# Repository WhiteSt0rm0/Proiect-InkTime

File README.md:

# Proiect InkTime

An affordable, open-source smartwatch powered by the nRF52840 with an e-paper display, designed for low power consumption and BLE connectivity.

## Table of Contents

1. [Hardware Diagram](#hardware-diagram)
2. [Bill of Materials](#bill-of-materials-bom)
3. [Hardware Description](#hardware-description)
4. [Pin Assignment](#nrf52840-pin-assignment)
5. [PCB Design Details](#pcb-design-details)

---

## Hardware Diagram

The InkTime smartwatch is built around the Nordic nRF52840 microcontroller and features the following subsystems:

```
                                    ┌───────────────────┐
                                    │    USB-C (J4)     │
                                    └──┬─────────────┬──┘
                                 VBUS  │             │ D+, D-
                                       │      ┌──────▼────────┐
                          ┌────────────┤      │  USBLC6 (D3)  │
                          │            │      │ ESD Protection│
                          │            │      └──────┬────────┘
                          │            │             │ D+, D- (protected)
                   ┌──────▼────────┐   │      ┌──────▼─────────────────────────┐
                   │  BQ25180 (IC3)│   │      │                                │
                   │  LiPo Charger │   │      │        nRF52840 (NRF52840_QF)  │
                   │  (I2C config) │   │      │        ARM Cortex-M4F @ 64MHz  │
                   └──────┬────────┘   │      │        BLE 5.0                 │
                          │            │      │                                │
                    VBAT  │     VBUS   │      │  ┌─────────────────────────┐   │
          ┌───────────────┤◄───────────┘      │  │ Interfaces:             │   │
          │               │                   │  │  SPI  → E-Paper Display │   │
   ┌──────▼────────┐      │                   │  │  I2C  → BMA423, DRV2605 │   │
   │ LiPo Battery  │      │                   │  │         MAX17048,       │   │
   │ LP502030      │      │                   │  │         BQ25180, RT6160 │   │
   │ 3.7V / 250mAh │      │                   │  │  USB  → USB-C (J4)      │   │
   └──────┬────────┘      │                   │  │  GPIO → Buttons, EPD    │   │
          │ VBAT          │                   │  │         ctrl, Haptic EN │   │
   ┌──────▼────────┐      │                   │  │  SWD  → TC2030 (J1)     │   │
   │ MAX17048 (U1) │──────│── I2C ───────────►│  └─────────────────────────┘   │
   │ Fuel Gauge    │      │                   │                                │
   │ (ALERT → GPIO)│      │                   │◄──── 32MHz Crystal (X1)        │
   └───────────────┘      │                   │◄──── 32.768kHz Crystal (X2)    │
                          │                   │◄──── 2.4GHz Antenna (ANT1)     │
                   ┌──────▼────────┐          │      via matching network      │
                   │  RT6160 (IC1) │          │      (L1, C3, C4, C9)          │
                   │  DC/DC        │          │                                │
                   │  Buck-Boost   │ VREG/3V3 │                                │
                   │  (I2C config) ├─────────►│                                │
                   └───────────────┘          └──┬──────┬──────┬───────────┬───┘
                                                 │      │      │           │
                              SPI (MOSI,SCK,CS)  │      │      │           │ GPIO
                              + GPIO ctrl        │      │ I2C  │ I2C       │ (SW_UP P0.26)
                                                 │      │      │           │ (SW_DN P0.27)
                  ┌──────────────────────┐       │      │      │       ┌───▼──────────────────┐
                  │  1.54" E-Paper (J2)  │◄──────┘      │      │       │  3×        Buttons   │
                  │  200×200px SPI       │              │      │       │  EVP-AKE31A          │
                  │                      │              │      │       │  (SW_ENT P1.00)      │
                  │  EPD Boost Circuit:  │              │      │       └──────────────────────┘
                  │  Q1 (DMG2305UX)      │              │      │
                  │  Q3 (SI1308EDL)      │       ┌──────▼──┐   │
                  │  D2,D4,D5 (MBR0530)  │       │ BMA423  │   │
                  │  L5 (68µH)           │       │  (IC2)  │   │
                  │  → PREVGH, PREVGL    │       │  IMU    │   │
                  └──────────────────────┘       └─────────┘   │
                                                        ┌──────▼──────┐
                           ┌──────────────┐             │  DRV2605    │
                           │  TC2030 (J1) │             │   (IC4)     │
                           │  SWD Debug   │             │  Haptic     │
                           │  (SWDIO,     │             │  Driver     │
                           │   SWDCLK,    │             │  + Motor    │
                           │   SWO, RST)  │             │  (FIT0774)  │
                           └──────────────┘             └─────────────┘
```

---

## Bill of Materials (BOM)

| Component | Value / Part Number | Package | Qty | Description | Datasheet |
|-----------|---------------------|---------|-----|-------------|-----------|
| NRF52840_QF | nRF52840 | QFN-73 | 1 | MCU with BLE 5.0 | [Link](datasheet-link) |
| IC1 | RT6160 | AWSCWL-CSP-15 | 1 | DC/DC Buck-Boost Converter | [Link](datasheet-link) |
| IC2 | BMA423 | LGA-12 | 1 | Triaxial Accelerometer (IMU) | [Link](datasheet-link) |
| IC3 | BQ25180 | YBGRDS-BGA-8 | 1 | LiPo Charger | [Link](datasheet-link) |
| IC4 | DRV2605 | YZFR-WCSP-9 | 1 | Haptic Driver | [Link](datasheet-link) |
| U1 | MAX17048 | G+T10-TDFN-8 | 1 | Fuel Gauge | [Link](datasheet-link) |
| D3 | USBLC6-2SC6Y | SOT-23-6 | 1 | ESD Protection | [Link](datasheet-link) |
| ANT1 | 2450AT18B100E | SMD | 1 | 2.4GHz Chip Antenna | [Link](datasheet-link) |
| X1 | 32MHz Crystal | SMD 2016 | 1 | Main Clock | - |
| X2 | 32.768kHz Crystal | SMD 3215 | 1 | RTC Clock | - |
| J1 | TC2030-IDC | Tag-Connect | 1 | SWD Debug Header | [Link](datasheet-link) |
| J2 | 503480-2400 | FPC-24 | 1 | E-Paper FPC Connector | [Link](datasheet-link) |
| J4 | KH-TYPE-C-16P | SMD | 1 | USB-C Connector | - |
| Q1 | DMG2305UX-7 | SOT-23 | 1 | P-Ch MOSFET (EPD drive) | [Link](datasheet-link) |
| Q3 | SI1308EDL-T1-GE3 | SC-70 | 1 | N-Ch MOSFET (EPD drive) | [Link](datasheet-link) |
| D2, D4, D5 | MBR0530 | SOD-123 | 3 | Schottky Diode (EPD drive) | - |
| L1 | 3.9nH | SMD 2012 | 1 | RF Matching Network | - |
| L2 | 10µH | SMD 2012 | 1 | nRF Power Inductor | - |
| L3 | 15nH | SMD 2012 | 1 | RF Filter | - |
| L5 | 68µH | SMD 2012 | 1 | EPD Boost Inductor | - |
| L7 | FTC252012SR47M-BCA | SMD 2012 | 1 | DC/DC Power Inductor (0.47µH) | - |
| SW_UP, SW_DN, SW_ENT | EVP-AKE31A | SMD | 3 | Tactile Buttons | - |
| SJ1 | Solder Jumper | SMD | 1 | Configuration Jumper | - |
| R1, R2, R5 | 0Ω | 0201 | 3 | Zero-ohm Resistors | - |
| R3, R4 | 3.3kΩ | 0201 | 2 | I2C Pull-up Resistors | - |
| R6, R2_EP_DR, R_PWR_EPD | 10kΩ | 0201 | 3 | Pull-up/Pull-down | - |
| R7, R8, R9 | 10kΩ | 0201 | 3 | Button Pull-down Resistors | - |
| R1_USB, R2_USB | 5.1kΩ | 0201 | 2 | USB-C CC Pull-down | - |
| R_TYPE_SEL | 2.2Ω | 0201 | 1 | EPD Type Select | - |
| R1_EP_DR | 0.47Ω | 0201 | 1 | EPD Current Sense | - |
| C1, C2, C17, C18 | 12pF | 0201 | 4 | Crystal Load Capacitors | - |
| C3, C4 | 1pF | 0201 | 2 | RF Matching | - |
| C9 | 820pF | 0201 | 1 | RF Matching | - |
| C5, C7, C8, C12, C19 | 100nF | 0201 | 5 | Decoupling Capacitors | - |
| C11 | 100pF | 0201 | 1 | Decoupling (DEC5) | - |
| C16 | 47nF | 0201 | 1 | Decoupling | - |
| C15 | 1.0µF | 0402 | 1 | Decoupling | - |
| C6, C14, C20, C21, C43, C2_EP_DR | 4.7µF | 0402 | 6 | Bulk Capacitors | - |
| C24, C39, C1_EP_DR | 10µF | 0402 | 3 | Input/Output Caps | - |
| C25, C33 | 22µF | 0402 | 2 | DC/DC Output Caps | - |
| C23, C27, C34, C42, EPD_C5 | 0.1µF | 0201 | 5 | Decoupling | - |
| C29-C32, C37, C38, EPD_C1-C12 | 1µF | 0402 | 15 | Filter/Bypass Caps | - |
| C10, C13, C22 | N.C. | 0201 | 3 | Do Not Populate | - |
| Test Pads | - | SMD | 14 | TP_GND, TP_3V3, TP_VBAT, etc. | - |

---

## Hardware Description

### Microcontroller — nRF52840 (NRF52840_QF)

The nRF52840 is the core of the InkTime, providing Bluetooth Low Energy 5.0 connectivity, ARM Cortex-M4F processing at 64MHz, and extensive GPIO. It communicates with peripherals via I2C and SPI buses and is powered by 3.3V from the RT6160 DC/DC converter.

Two crystals provide clock sources: a 32MHz crystal (X1) connected to XC1/XC2 with 12pF load capacitors (C1, C2), and a 32.768kHz crystal (X2) connected to P0.00/XL1 and P0.01/XL2 with 12pF load capacitors (C17, C18).

The RF section uses a 2450AT18B100E chip antenna connected through an impedance matching network (L1=3.9nH, C3=1pF, C4=1pF, C9=820pF) to the ANT pin. The antenna is placed at the edge of the PCB with a copper keepout zone on all layers underneath.

Decoupling capacitors placed close to corresponding power pins: C5 (100nF) on DEC1, C8 (100nF) on DEC3, C7 (100nF) on DEC4_6, C11 (100pF) on DEC5, C15 (1.0µF). Capacitors C10, C13, C22 are N.C. (Do Not Populate) per Nordic's reference design.

### Power Management

**LiPo Charger — BQ25180 (IC3):** Manages battery charging from USB-C (VBUS). Single-cell LiPo battery connected directly to test pads (TP_VBAT, TP_BAT_GND). I2C configurable. Interrupt output (PMIC_INT) to nRF52840. Bypass capacitors C37 (1µF), C39 (10µF). Pull-up R6 (10kΩ) on TS/MR.

**DC/DC Converter — RT6160 (IC1):** Buck-boost converter, VBAT (3.0–4.2V) to VREG/3V3. I2C voltage selection via VSEL pin. Power inductor L7 (0.47µH). Input cap C23 (0.1µF), output caps C24 (10µF), C25 (22µF), C33 (22µF). I2C pull-ups R3, R4 (3.3kΩ).

**Fuel Gauge — MAX17048 (U1):** Battery monitoring via I2C. CELL pin to VBAT, ALERT output to nRF52840. Bypass cap C38 (1µF).

### Display — 1.54" E-Paper

Connected via J2 (503480-2400). Uses an SPI interface (MOSI, SCK, EPD_CS). The drive circuit features Q3 (SI1308EDL), Q1 (DMG2305UX), diodes D2/D4/D5 (MBR0530), inductor L5 (68µH), and capacitors EPD_C1–C12 for high-voltage generation (PREVGH, PREVGL). Control signals include EPD_RST, EPD_BUSY, and EPD_DC.

### IMU — BMA423 (IC2)

Triaxial accelerometer connected via I2C (SDA, SCL). Provides two interrupt outputs (IMU_INT1, IMU_INT2) for motion/step/gesture detection. Features a decoupling C19 (100nF) and zero-ohm resistors R1, R2, R5 for pin configuration.

### Haptic Driver — DRV2605 (IC4)

I2C haptic driver for the vibration motor (FIT0774). Enabled via the HAPTIC_EN GPIO pin. Includes decoupling capacitors C32 (1µF) and C34 (0.1µF).

### USB-C and ESD Protection

Features a KH-TYPE-C-16P connector (J4) with USBLC6-2SC6Y (D3) for ESD protection. Includes CC pull-downs R1_USB, R2_USB (5.1kΩ) and bypass caps C42 (0.1µF), C43 (4.7µF).

### SWD Debug — TC2030-IDC (J1)

Utilizes a Tag-Connect pogo-pin interface: SWDIO, SWDCLK, SWO, RESET, 3.3V, GND. This allows for debugging without requiring a permanent connector on the board.

---

## nRF52840 Pin Assignment

| Pin | Signal | Function | Interface |
|-----|--------|----------|-----------|
| P0.00/XL1 | XL1 | 32.768kHz Crystal | Clock |
| P0.01/XL2 | XL2 | 32.768kHz Crystal | Clock |
| P0.04/AIN2 | IMU_INT1 | BMA423 Interrupt 1 | GPIO |
| P0.05/AIN3 | IMU_INT2 | BMA423 Interrupt 2 | GPIO |
| P0.06 | EPD_CS | E-Paper Chip Select | SPI |
| P0.07 | EPD_DC | E-Paper Data/Command | GPIO |
| P0.08 | EPD_RST | E-Paper Reset | GPIO |
| P0.09/NFC1 | PMIC_INT | BQ25180 Interrupt | GPIO |
| P0.11 | SCK | SPI Clock (E-Paper) | SPI |
| P0.12 | MOSI | SPI Data (E-Paper) | SPI |
| P0.13 | EPD_BUSY | E-Paper Busy | GPIO |
| P0.14 | SCL | I2C Clock | I2C |
| P0.15 | SDA | I2C Data | I2C |
| P0.18/RESET | RESET | System Reset | Reset |
| P0.19 | HAPTIC_EN | DRV2605 Enable | GPIO |
| P0.26 | SW_UP | Button Up | GPIO |
| P0.27 | SW_DN | Button Down | GPIO |
| P1.00 | SW_ENT | Button Enter | GPIO |
| P1.01 | ALERT | MAX17048 Alert | GPIO |
| P1.09 | SWO | Debug Trace Output | Debug |
| XC1/XC2 | Crystal | 32MHz Oscillator | Clock |
| ANT | RF | Antenna via matching | RF |
| VBUS | USB_VBUS | USB Power (5V) | Power |
| D+/D- | USB Data | USB Data Lines | USB |
| SWDIO | Debug | SWD Data | Debug |
| SWDCLK | Debug | SWD Clock | Debug |

**Note:** The I2C Bus is shared by BMA423 (IC2), BQ25180 (IC3), RT6160 (IC1), DRV2605 (IC4), and MAX17048 (U1). It uses pull-ups R3, R4 (3.3kΩ) to 3V3.

---

## PCB Design Details

### Board Specifications

- **Dimensions:** 46mm × 35mm, rounded corners
- **Layers:** 4 (Top, Route2, Route63, Bottom)
- **Thickness:** 1.0mm
- **Trace widths:** 0.15mm (signals), 0.3mm (power)
- **Components:** All mounted on the TOP layer

### Layer Stack

| Layer | Name | Function |
|-------|------|----------|
| 1 | Top | Signals + GND polygon |
| 2 | Route2 | Dedicated GND plane |
| 6 | Route63 | Signal routing |
| 4 | Bottom | Signals + GND polygon |

### Design Decisions and Accepted Errors

**Copper Width Errors:** Power nets (3V3, VREG, VBAT, VBUS, etc.) require 0.3mm trace width per design rules. However, in dense areas—particularly around small IC packages and tight pad spacing—there is not enough physical space to maintain this width. These resulting DRC errors were manually verified and accepted.

**Copper Clearance Errors:** In highly congested areas (around the nRF52840 BGA and passive component clusters), some traces and pads violate the 0.15mm clearance rule. These occur where component placement leaves no alternative routing path and were accepted after confirming no actual shorts exist.

**Overlapping / Polygon Clearance Errors:** Some GND polygons on different layers generate clearance warnings where they overlap. These are non-functional warnings, as the polygons belong to the same net (GND).

**Board Outline Clearance Errors:** The three tactile buttons (SW_UP, SW_DN, SW_ENT) and the USB-C connector (J4) intentionally extend beyond the PCB edge for mechanical alignment with the enclosure cutouts. This is by design.

**N.C. Capacitors:** Footprints (C10, C13, C22) are present but intentionally not populated per Nordic's reference design.

**Silkscreen:** Proper labeling is applied to ICs, connectors, test pads, and capacitors.

**Via Stitching:** GND vias are distributed across the board between all ground planes, with a higher concentration around the nRF52840 and RF antenna area to ensure low-impedance ground return paths at 2.4GHz.

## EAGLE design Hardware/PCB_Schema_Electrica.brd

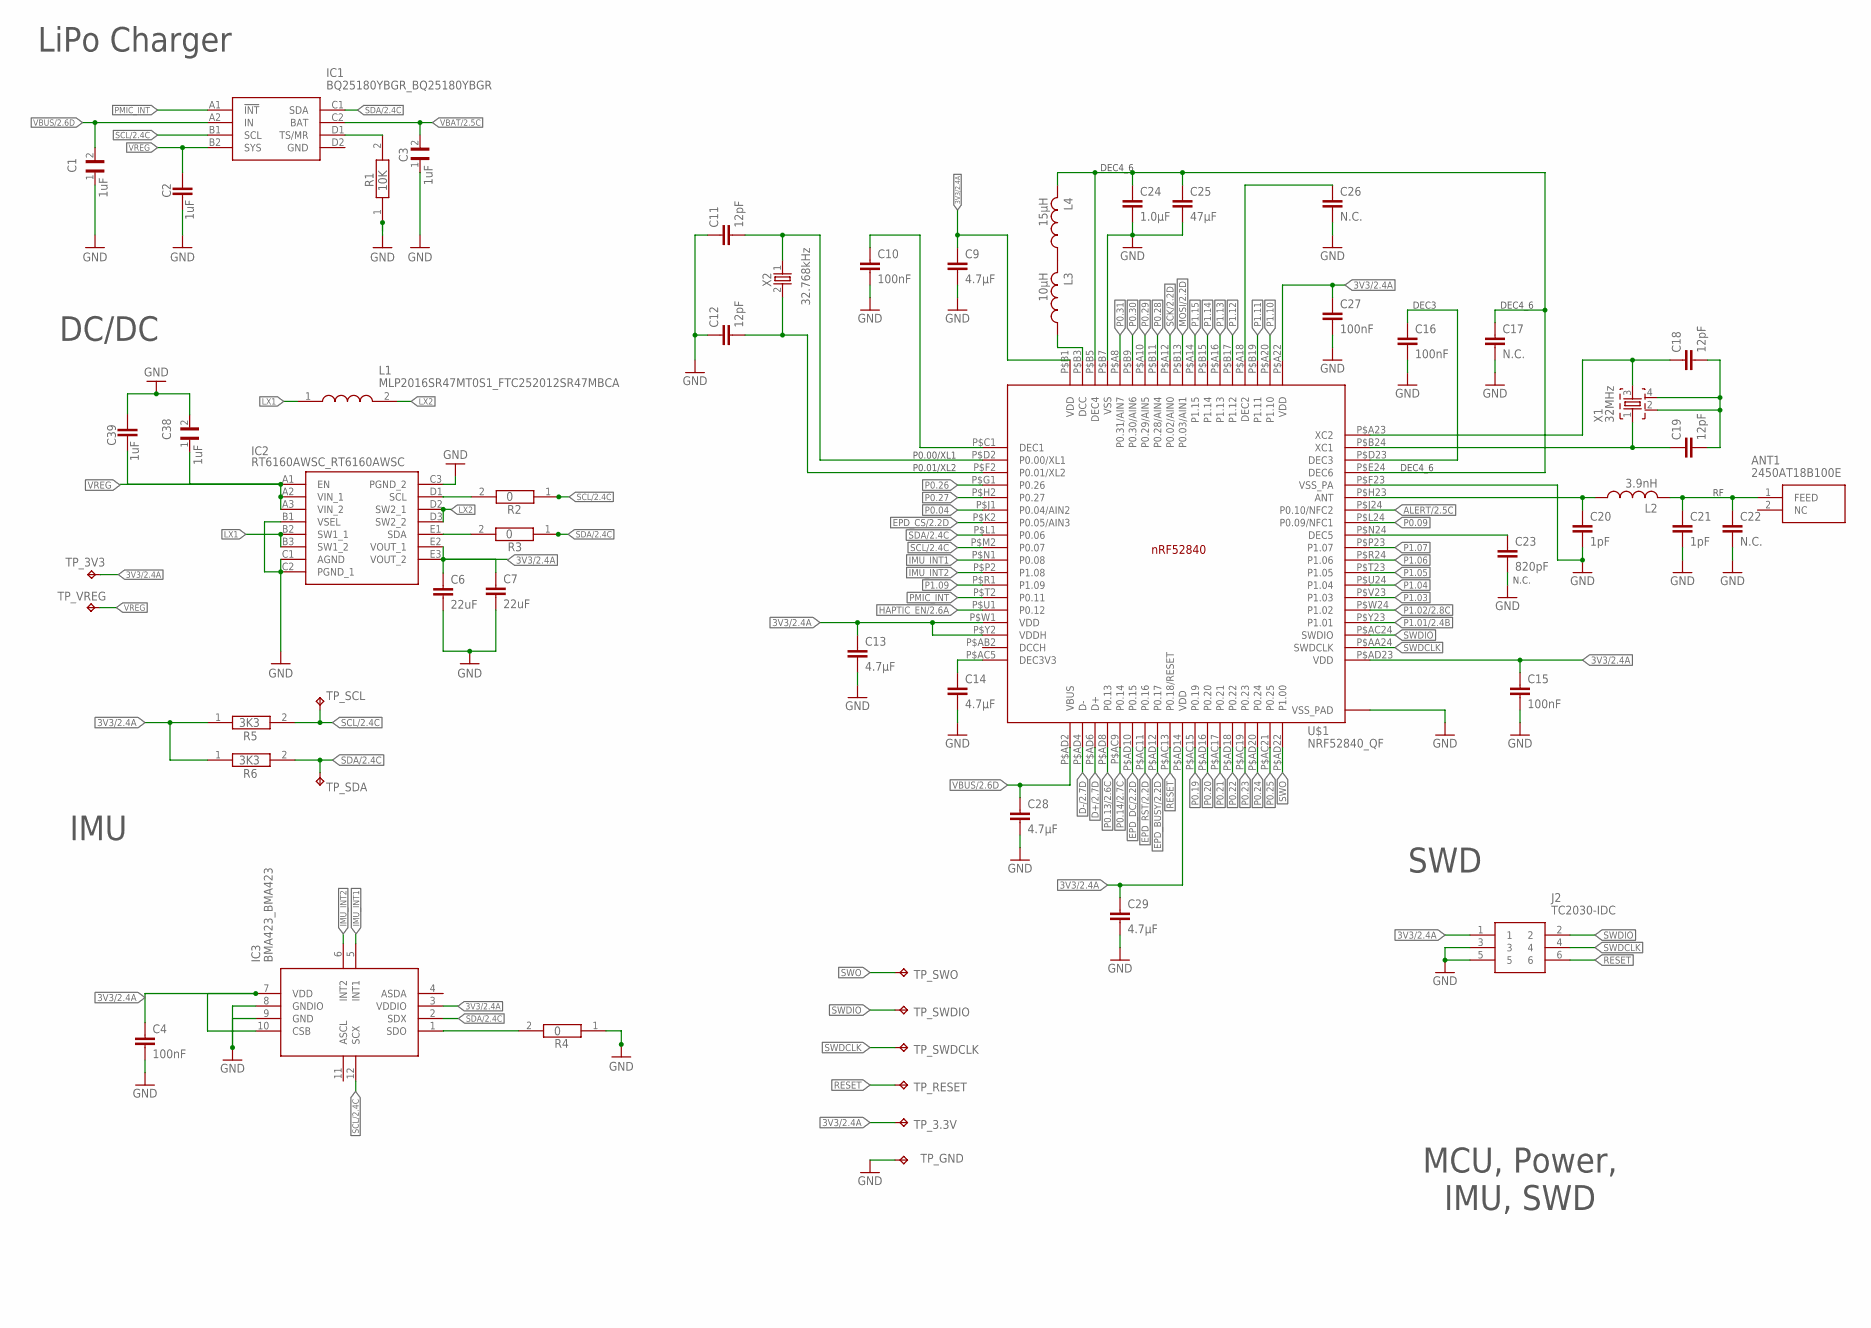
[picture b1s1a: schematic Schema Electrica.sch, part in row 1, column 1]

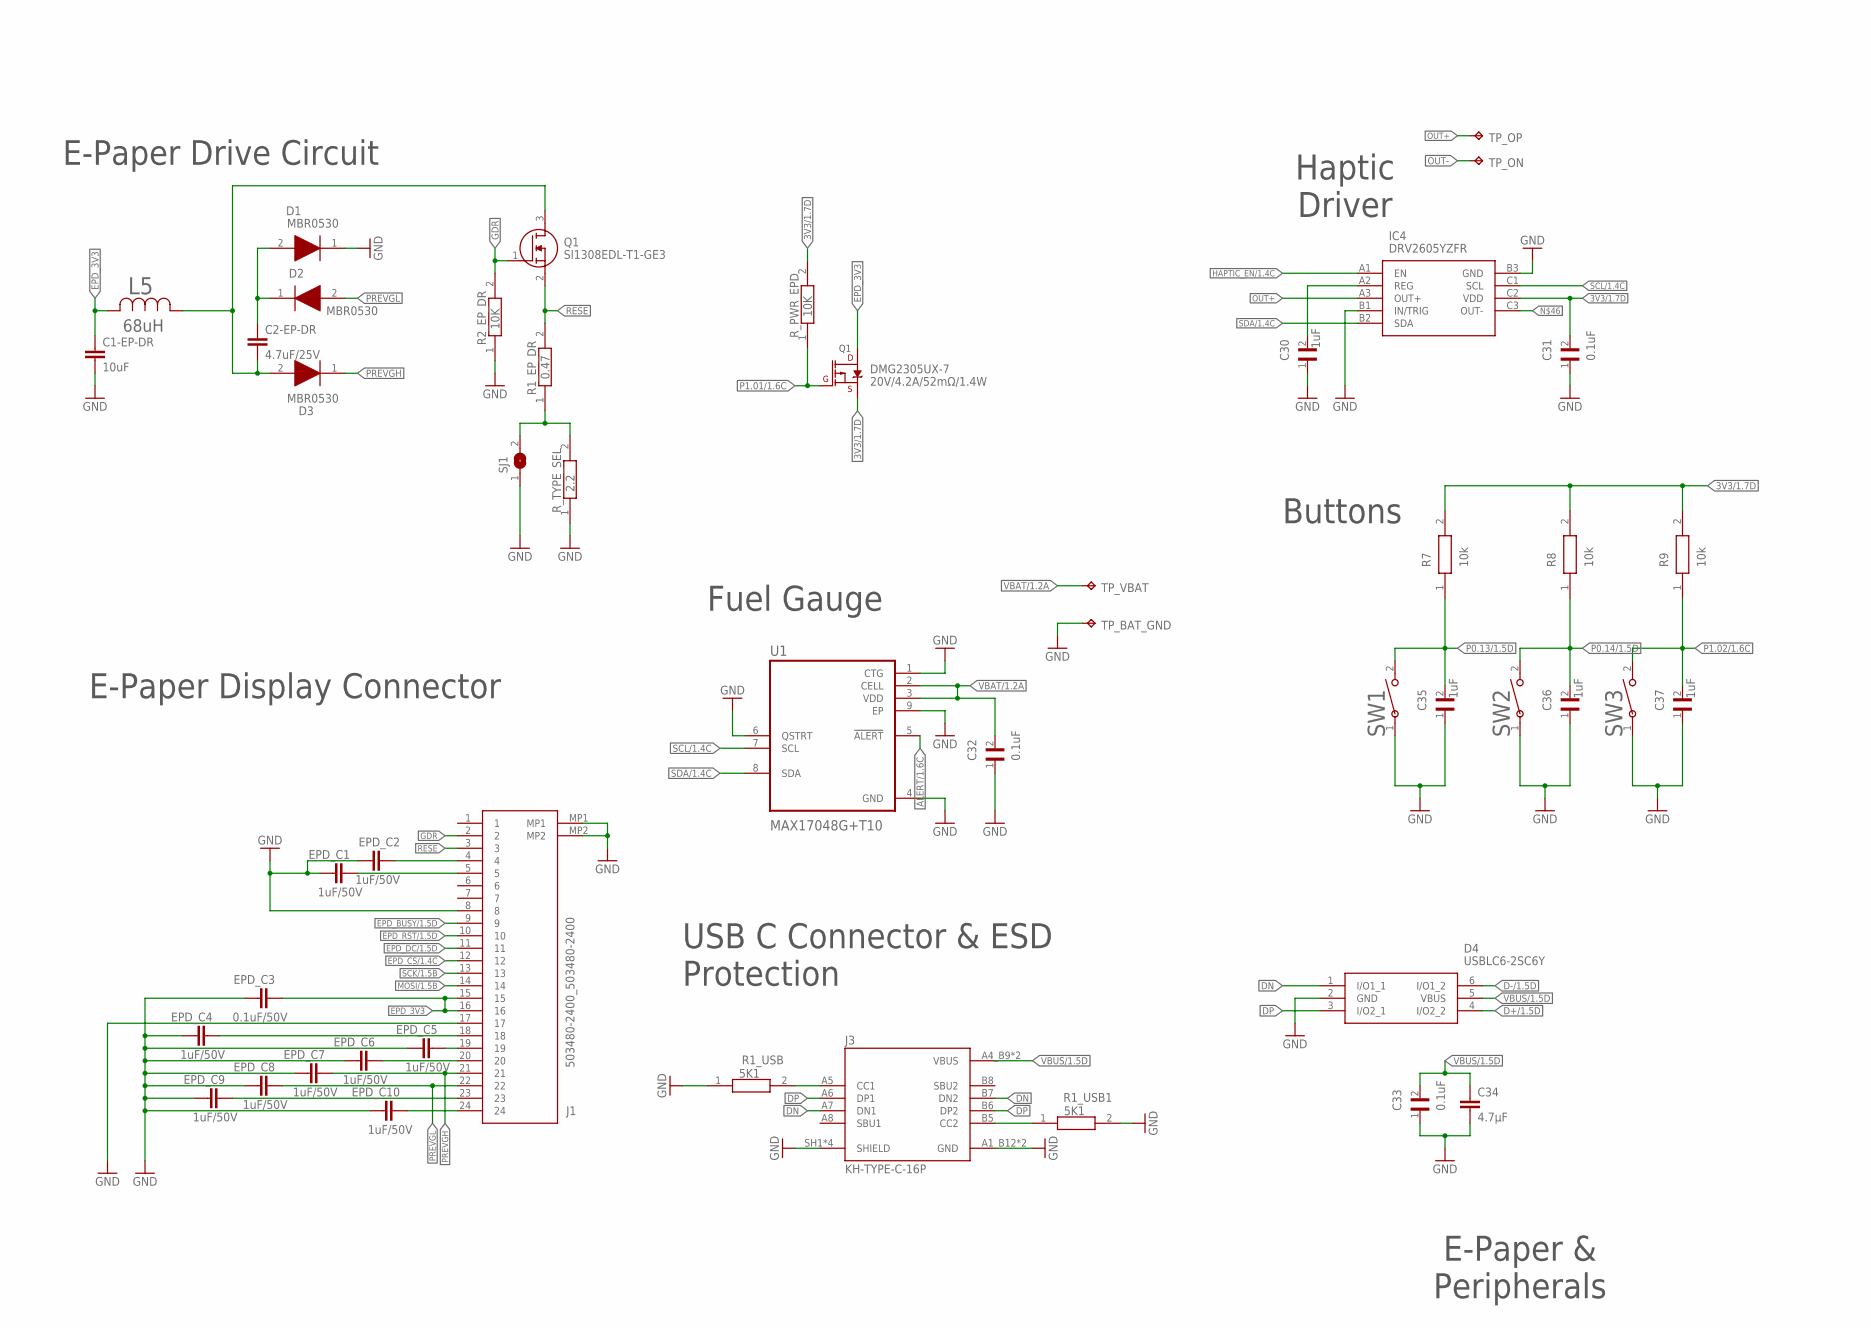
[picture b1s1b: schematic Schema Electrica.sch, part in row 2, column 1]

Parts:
ANT1: 2450AT18B100E; 2450AT18B100E_ANTC3216X140N
C1, C3, C30, C35, C36, C37, C38: 1uF; GRM011R60J152KE01L_1_0201
C1-EP-DR: 10uF; PERFECT_0402_0402
C2, C39: 1uF; PERFECT_0402_0402
C2-EP-DR: 4.7uF/25V; PERFECT_0402_0402
C4, C10, C15, C16, C27: 100nF; PERFECT_0402_0402
C6, C7: 22uF; PERFECT_0402_0402
C9, C13, C14, C28, C29, C34: 4.7µF; PERFECT_0402_0402
C11, C12, C18, C19: 12pF; PERFECT_0402_0402
C17, C22, C26: N.C.; PERFECT_0402_0402
C20, C21: 1pF; PERFECT_0402_0402
C23: 820pF; PERFECT_0402_0402
C24: 1.0µF; PERFECT_0402_0402
C25: 47µF; PERFECT_0402_0402
C31, C32, C33: 0.1uF; GRM011R60J152KE01L_1_0201
D1, D2, D3: MBR0530; ESP32_C6_LIBRARY_5_SOD3716X135N
D4: USBLC6-2SC6Y; ESP32_C6_LIBRARY_3_SOT95P280X145-6N
DMG2305UX-7: 20V/4.2A/52mΩ/1.4W; ESP32_C6_LIBRARY_4_ESP32_C6_LIBRARY_4_ESP32_C6_LIBRARY_4_ES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
EPD_C1, EPD_C2, EPD_C4, EPD_C5, EPD_C6, EPD_C7, EPD_C8, EPD_C9, EPD_C10: 1uF/50V; PERFECT_0402_0402
EPD_C3: 0.1uF/50V; PERFECT_0402_0402
IC1: BQ25180YBGR_BQ25180YBGR; BQ25180YBGR_BGA8C40P2X4_100X155X50
IC2: RT6160AWSC_RT6160AWSC; RT6160AWSC_BGA15C40P3X5_140X230X60
IC3: BMA423_BMA423
IC4: DRV2605YZFR; DRV2605YZFR_BGA9C50P3X3_144X144X62
J1: 503480-2400_503480-2400; 503480-2400_5034802400
J2: TC2030-IDC; TC2030-IDC_TC2030IDC
J3: KH-TYPE-C-16P; KH-TYPE-C-16P_KINGHELM_KH-TYPE-C-16P
L1: MLP2016SR47MT0S1_FTC252012SR47MBCA; MLP2016SR47MT0S1_INDC2016X100N
L2: 3.9nH; NORDIC_NRF_2_RESC0402_L
L3: 10µH; NORDIC_NRF_2_RESC0402_L
L4: 15µH; NORDIC_NRF_2_RESC0402_L
L5: 68uH; ESP32_C6_LIBRARY_2_IND_4828-WE-TPC_WRE
Q1: SI1308EDL-T1-GE3; ESP32_C6_LIBRARY_6_SOT65P210X110-3N
R1, R2_EP_DR: 10K; CPF0201D7K68C1_0201
R1_EP_DR: 0.47; CPF0201D7K68C1_0201
R1_USB, R1_USB1: 5K1; CPF0201D7K68C1_0201
R2, R3: 0; CPF0201D7K68C1_0201
R4: 0; ERA-1AEB3401C_0201
R5, R6: 3K3; CPF0201D7K68C1_0201
R7, R8, R9: 10k; ERA-1AEB3401C_0201
R_PWR_EPD: 10K; CPF0201D7K68C1_0201
R_TYPE_SEL: 2.2; CPF0201D7K68C1_0201
SJ1: ESP32_C6_LIBRARY_7_JUMPER_SJ
SW1, SW2, SW3: 2025-10-22_07-23-44_LIBRARY_EVP-AKE31ASW_EVP-AKE3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; 2025-10-22_07-23-44_LIBRARY_SW_EVP-AKE31A_PAN
TP_3.3V, TP_3V3: HECTOR_WATCH_1_TPTP20R; HECTOR_WATCH_1_TP20R
TP_BAT_GND: HECTOR_WATCH_1_TPTP20R; HECTOR_WATCH_1_TP20R
TP_GND: HECTOR_WATCH_1_TPTP20R; HECTOR_WATCH_1_TP20R
TP_ON: HECTOR_WATCH_1_TPTP20R; HECTOR_WATCH_1_TP20R
TP_OP: HECTOR_WATCH_1_TPTP20R; HECTOR_WATCH_1_TP20R
TP_RESET: HECTOR_WATCH_1_TPTP20R; HECTOR_WATCH_1_TP20R
TP_SCL: HECTOR_WATCH_1_TPTP20R; HECTOR_WATCH_1_TP20R
TP_SDA: HECTOR_WATCH_1_TPTP20R; HECTOR_WATCH_1_TP20R
TP_SWDCLK: HECTOR_WATCH_1_TPTP20R; HECTOR_WATCH_1_TP20R
TP_SWDIO: HECTOR_WATCH_1_TPTP20R; HECTOR_WATCH_1_TP20R
TP_SWO: HECTOR_WATCH_1_TPTP20R; HECTOR_WATCH_1_TP20R
TP_VBAT: HECTOR_WATCH_1_TPTP20R; HECTOR_WATCH_1_TP20R
TP_VREG: HECTOR_WATCH_1_TPTP20R; HECTOR_WATCH_1_TP20R
U1: MAX17048G+T10; ESP32_C6_LIBRARY_SON50P200X200X80-9N
U$1: NRF52840_QF; NORDIC_NRF_4_AQFN50P700X700X85_HS-74N
X1: 32MHz; NORDIC_NRF_BT-XTAL_2016_N
X2: 32.768kHz; NORDIC_NRF_1_XTAL_3215_N

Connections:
3V3/1.7D: C31.2, DMG2305UX-7.2 (S), IC4.C2 (VDD), R7.2, R8.2, R9.2, R_PWR_EPD.2
3V3/2.4A: C4.1, C6.1, C7.1, C9.1, C13.1, C15.1, C27.1, C29.1, IC2.E2 (VOUT_1), IC2.E3 (VOUT_2), IC3.3 (VDDIO), IC3.7 (VDD), IC3.10 (CSB), J2.1, R5.1, R6.1, TP_3.3V.TP, TP_3V3.TP, U$1.P$A22 (VDD), U$1.P$AD14 (VDD), U$1.P$AD23 (VDD), U$1.P$B1 (VDD), U$1.P$W1 (VDD), U$1.P$Y2 (VDDH)
ALERT/1.6C: U1.5 (!ALERT)
ALERT/2.5C: U$1.P$J24 (P0.10/NFC2)
D+/1.5D: D4.4 (I/O2_2)
D+/2.7D: U$1.P$AD6 (D+)
D-/1.5D: D4.6 (I/O1_2)
D-/2.7D: U$1.P$AD4 (D-)
DEC3: C16.1, U$1.P$D23 (DEC3)
DN: D4.1 (I/O1_1), J3.A7 (DN1), J3.B7 (DN2)
DP: D4.3 (I/O2_1), J3.A6 (DP1), J3.B6 (DP2)
EPD_3V3: C1-EP-DR.1, DMG2305UX-7.3 (D), EPD_C3.2, J1.15, J1.16, L5.2
EPD_BUSY/1.5D: J1.9
EPD_BUSY/2.2D: U$1.P$AD12 (P0.17)
EPD_CS/1.4C: J1.12
EPD_CS/2.2D: U$1.P$K2 (P0.05/AIN3)
EPD_DC/1.5D: J1.11
EPD_DC/2.2D: U$1.P$AD10 (P0.15)
EPD_RST/1.5D: J1.10
EPD_RST/2.2D: U$1.P$AC11 (P0.16)
GDR: J1.2, Q1.1 (G), R2_EP_DR.2
GND: C1.1, C1-EP-DR.2, C2.2, C3.1, C4.2, C6.2, C7.2, C9.2, C10.2, C11.1, C12.1, C13.2, C14.2, C15.2, C16.2, C17.2, C20.2, C21.2, C22.2, C23.2, C24.2, C25.2, C26.2, C27.2, C28.2, C29.2, C30.1, C31.1, C32.1, C33.1, C34.2, C35.1, C36.1, C37.1, C38.2, C39.1, D1.1 (K), D4.2 (GND), EPD_C1.1, EPD_C2.1, EPD_C3.1, EPD_C4.1, EPD_C5.1, EPD_C6.1, EPD_C7.1, EPD_C8.1, EPD_C9.1, EPD_C10.1, IC3.8 (GNDIO), IC3.9 (GND), IC4.B1 (IN/TRIG), IC4.B3 (GND), J1.8, J1.17, J1.MP1, J1.MP2, J2.3, J2.5, J3.A1_B12 (GND), J3.A12_B1 (GND), J3.SH1 (SHIELD), J3.SH2 (SHIELD), J3.SH3 (SHIELD), J3.SH4 (SHIELD), R1.1, R1_USB.1, R1_USB1.2, R2_EP_DR.1, R4.1, R_TYPE_SEL.1, SJ1.1, SW1.1, SW2.1, SW3.1, TP_BAT_GND.TP, TP_GND.TP, U1.1 (CTG), U1.4 (GND), U1.6 (QSTRT), U1.9 (EP), U$1.P$74 (VSS_PAD), U$1.P$75 (VSS_PAD), U$1.P$76 (VSS_PAD), U$1.P$77 (VSS_PAD), U$1.P$78 (VSS_PAD), U$1.P$79 (VSS_PAD), U$1.P$80 (VSS_PAD), U$1.P$81 (VSS_PAD), U$1.P$82 (VSS_PAD), U$1.P$83 (VSS_PAD), U$1.P$84 (VSS_PAD), U$1.P$85 (VSS_PAD), U$1.P$86 (VSS_PAD), U$1.P$87 (VSS_PAD), U$1.P$88 (VSS_PAD), U$1.P$89 (VSS_PAD), U$1.P$90 (VSS_PAD), U$1.P$B7 (VSS), U$1.P$F23 (VSS_PA)
HAPTIC_EN/1.4C: IC4.A1 (EN)
HAPTIC_EN/2.6A: U$1.P$U1 (P0.12)
IMU_INT1: IC3.5 (INT1), U$1.P$N1 (P0.08)
IMU_INT2: IC3.6 (INT2), U$1.P$P2 (P1.08)
LX1: IC2.B2 (SW1_1), IC2.B3 (SW1_2), L1.1
LX2: IC2.D2 (SW2_1), IC2.D3 (SW2_2), L1.2
MOSI/1.5B: J1.14
MOSI/2.2D: U$1.P$B13 (P0.03/AIN1)
unnamed: IC1.D1 (TS/MR), R1.2
unnamed: IC2.D1 (SCL), R2.2
unnamed: IC2.E1 (SDA), R3.2
unnamed: IC3.1 (SDO), R4.2
unnamed: IC2.B1 (VSEL), IC2.C1 (AGND), IC2.C2 (PGND_1)
unnamed: C10.1, U$1.P$C1 (DEC1)
unnamed: C11.2, U$1.P$D2 (P0.00/XL1), X2.1
unnamed: C12.2, U$1.P$F2 (P0.01/XL2), X2.2
unnamed: C14.1, U$1.P$AC5 (DEC3V3)
unnamed: C17.1, C24.1, C25.1, L4.2, U$1.P$B5 (DEC4), U$1.P$E24 (DEC6)
unnamed: C18.1, U$1.P$A23 (XC2), X1.3
unnamed: C18.2, C19.2, X1.2, X1.4
unnamed: C19.1, U$1.P$B24 (XC1), X1.1
unnamed: C20.1, L2.1, U$1.P$H23 (ANT)
unnamed: ANT1.1 (FEED), C21.1, C22.1, L2.2
unnamed: C23.1, U$1.P$N24 (DEC5)
unnamed: L3.1, U$1.P$B3 (DCC)
unnamed: C26.1, U$1.P$A18 (DEC2)
unnamed: L3.2, L4.1
unnamed: C2-EP-DR.1, D1.2 (A), D2.1 (K)
unnamed: C2-EP-DR.2, D3.2 (A), L5.1, Q1.3 (D)
unnamed: EPD_C2.2, J1.4
unnamed: EPD_C1.2, J1.5
unnamed: EPD_C4.2, J1.18
unnamed: EPD_C5.2, J1.19
unnamed: EPD_C6.2, J1.20
unnamed: J3.A5 (CC1), R1_USB.2
unnamed: R1_EP_DR.1, R_TYPE_SEL.2, SJ1.2
unnamed: EPD_C9.2, J1.23
unnamed: EPD_C10.2, J1.24
unnamed: C30.2, IC4.A2 (REG)
unnamed: J3.B5 (CC2), R1_USB1.1
OUT+: IC4.A3 (OUT+), TP_OP.TP
OUT-: TP_ON.TP
P0.04: U$1.P$J1 (P0.04/AIN2)
P0.09: U$1.P$L24 (P0.09/NFC1)
P0.13/1.5D: C35.2, R7.1, SW1.2
P0.13/2.6C: U$1.P$AD8 (P0.13)
P0.14/1.5D: C36.2, R8.1, SW2.2
P0.14/2.7C: U$1.P$AC9 (P0.14)
P0.19: U$1.P$AC15 (P0.19)
P0.20: U$1.P$AD16 (P0.20)
P0.21: U$1.P$AC17 (P0.21)
P0.22: U$1.P$AD18 (P0.22)
P0.23: U$1.P$AC19 (P0.23)
P0.24: U$1.P$AD20 (P0.24)
P0.25: U$1.P$AC21 (P0.25)
P0.26: U$1.P$G1 (P0.26)
P0.27: U$1.P$H2 (P0.27)
P0.28: U$1.P$B11 (P0.28/AIN4)
P0.29: U$1.P$A10 (P0.29/AIN5)
P0.30: U$1.P$B9 (P0.30/AIN6)
P0.31: U$1.P$A8 (P0.31/AIN7)
P1.01/1.6C: DMG2305UX-7.1 (G), R_PWR_EPD.1
P1.01/2.4B: U$1.P$Y23 (P1.01)
P1.02/1.6C: C37.2, R9.1, SW3.2
P1.02/2.8C: U$1.P$W24 (P1.02)
P1.03: U$1.P$V23 (P1.03)
P1.04: U$1.P$U24 (P1.04)
P1.05: U$1.P$T23 (P1.05)
P1.06: U$1.P$R24 (P1.06)
P1.07: U$1.P$P23 (P1.07)
P1.09: U$1.P$R1 (P1.09)
P1.10: U$1.P$A20 (P1.10)
P1.11: U$1.P$B19 (P1.11)
P1.12: U$1.P$B17 (P1.12)
P1.13: U$1.P$A16 (P1.13)
P1.14: U$1.P$B15 (P1.14)
P1.15: U$1.P$A14 (P1.15)
PMIC_INT: IC1.A1 (!INT), U$1.P$T2 (P0.11)
PREVGH: D3.1 (K), EPD_C7.2, J1.21
PREVGL: D2.2 (A), EPD_C8.2, J1.22
RESE: J1.3, Q1.2 (S), R1_EP_DR.2
RESET: J2.6, TP_RESET.TP, U$1.P$AC13 (P0.18/RESET)
SCK/1.5B: J1.13
SCK/2.2D: U$1.P$A12 (P0.02/AIN0)
SCL/1.4C: IC4.C1 (SCL), U1.7 (SCL)
SCL/2.4C: IC1.B1 (SCL), IC3.12 (SCX), R2.1, R5.2, TP_SCL.TP, U$1.P$M2 (P0.07)
SDA/1.4C: IC4.B2 (SDA), U1.8 (SDA)
SDA/2.4C: IC1.C1 (SDA), IC3.2 (SDX), R3.1, R6.2, TP_SDA.TP, U$1.P$L1 (P0.06)
SWDCLK: J2.4, TP_SWDCLK.TP, U$1.P$AA24 (SWDCLK)
SWDIO: J2.2, TP_SWDIO.TP, U$1.P$AC24 (SWDIO)
SWO: TP_SWO.TP, U$1.P$AD22 (P1.00)
VBAT/1.2A: C32.2, TP_VBAT.TP, U1.2 (CELL), U1.3 (VDD)
VBAT/2.5C: C3.2, IC1.C2 (BAT)
VBUS/1.5D: C33.2, C34.1, D4.5 (VBUS), J3.A4_B9 (VBUS), J3.A9_B4 (VBUS)
VBUS/2.6D: C1.2, C28.1, IC1.A2 (IN), U$1.P$AD2 (VBUS)
VREG: C2.1, C38.1, C39.2, IC1.B2 (SYS), IC2.A1 (EN), IC2.A2 (VIN_1), IC2.A3 (VIN_2), TP_VREG.TP

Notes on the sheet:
LiPo Charger
DC/DC
IMU
P0.00/XL1
P0.01/XL2
DEC3
DEC4_6
N.C.
E-Paper Drive Circuit
E-Paper Display Connector
Haptic Driver
Fuel Gauge
SWD
USB C Connector & ESD Protection
Buttons
MCU, Power, IMU, SWD
E-Paper & Peripherals

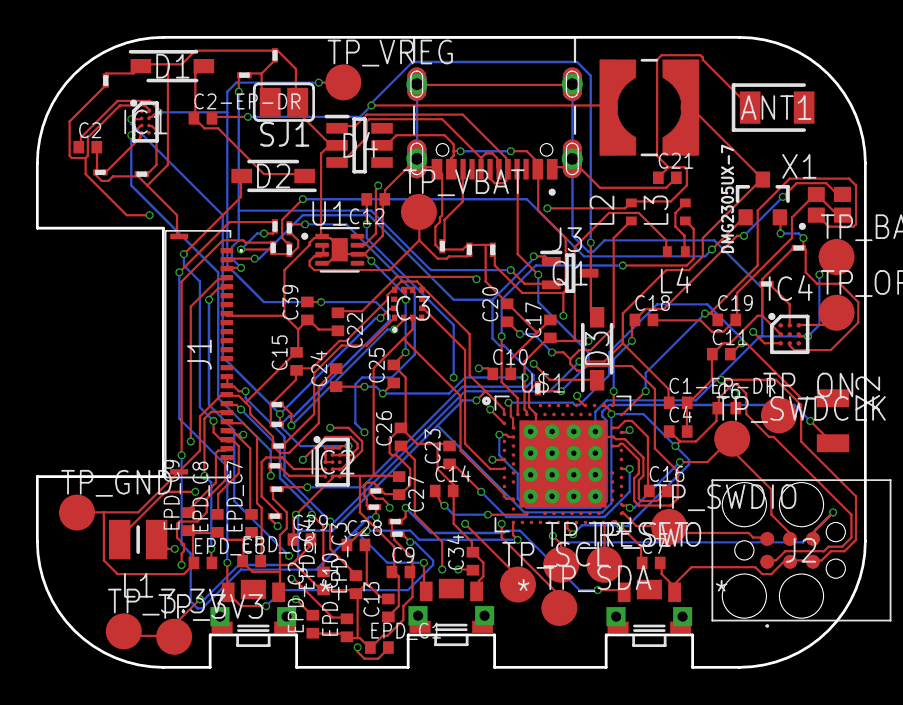
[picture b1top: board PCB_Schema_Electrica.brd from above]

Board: 4 copper layers, 46.0 x 35.0 mm, 105 parts (0 on the bottom side), 66 nets.

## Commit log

2026-04-08 commit 1, incomplete tasks
2026-04-22 solved issues
2026-04-22 Expand README with hardware details and design choices
    Added detailed hardware specifications, including diagrams, bill of materials, and design decisions for the InkTime smartwatch project.
2026-04-22 Revise README format and content
    Updated the README to improve structure and clarity, added a table of contents, and reformatted the Bill of Materials section.

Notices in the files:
parts and their libraries:
COPYRIGHT: Copyright (C) 2024 Ultra Librarian. All rights reserved.
COPYRIGHT: Copyright (C) 2025 Ultra Librarian. All rights reserved.
